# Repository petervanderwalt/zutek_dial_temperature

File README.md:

# zutek_dial_temperature
zutek_dial_temperature

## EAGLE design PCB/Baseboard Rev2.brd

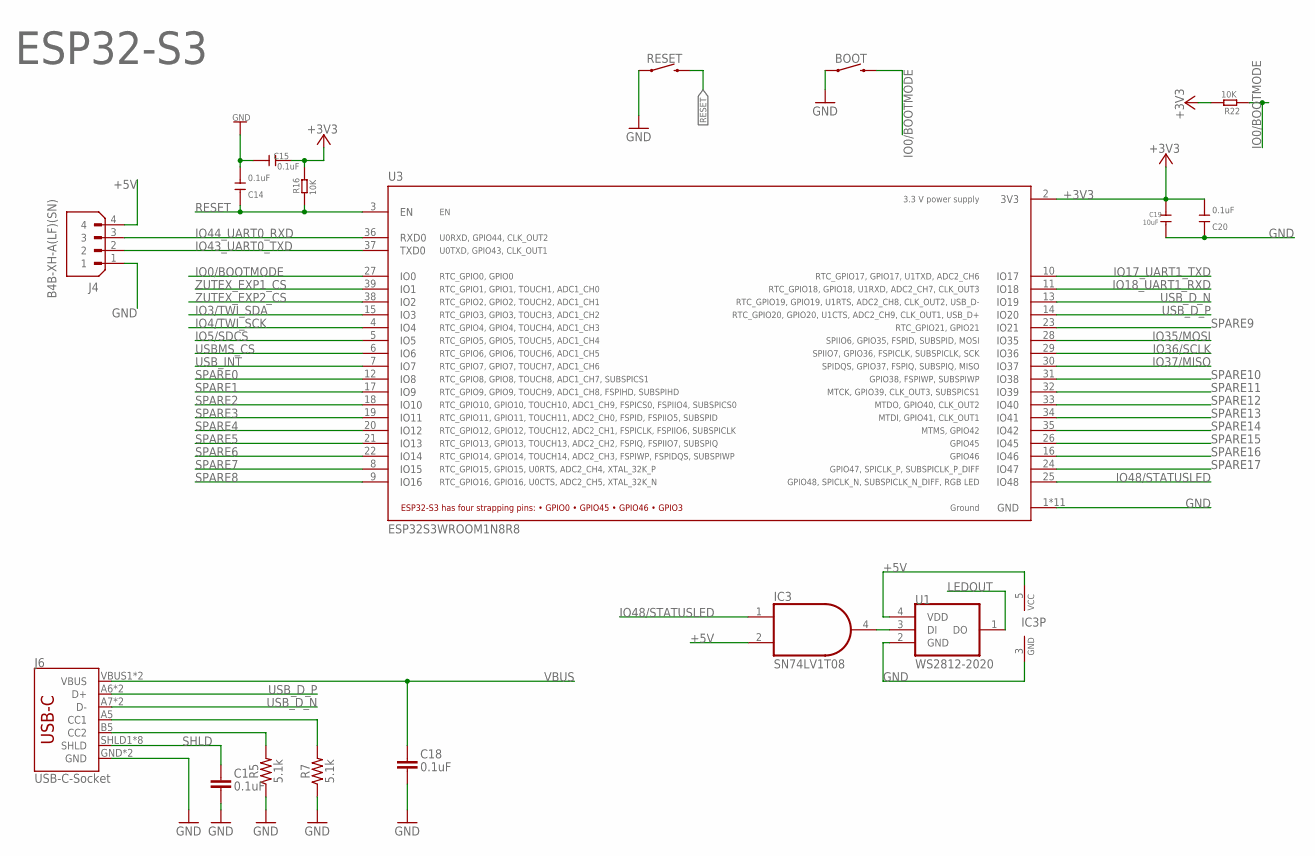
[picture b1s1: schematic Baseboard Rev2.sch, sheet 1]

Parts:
BOOT: MOMENTARY-SWITCH-SPST-SMD-6.0X3.5MM; TACTILE_SWITCH_SMD_6.0X3.5MM
C1, C18: 0.1uF; 0603-CAP
C14, C15, C20: 0.1uF; DISCRETE_C0603
C19: 10uF; C1206
IC3: SN74LV1T08; SOT23-5
J4: B4B-XH-A(LF)(SN); JST_B4B-XH-A(LF)(SN)
J6: USB-C-Socket; USB-C-16P
R5, R7: 5.1k; 0603@1
R16, R22: 10K; R0603
RESET: MOMENTARY-SWITCH-SPST-SMD-6.0X3.5MM; TACTILE_SWITCH_SMD_6.0X3.5MM
U1: WS2812-2020; LED_WS2812-2020
U3: ESP32S3WROOM1N8R8; XCVR_ESP32S3WROOM1N8R8

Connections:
+3V3: C15.1, C19.1, C20.2, R16.2, R22.2, U3.2 (3V3); also elsewhere on the board
+5V: IC3.2 (I1), IC3.5 (VCC), J4.4, U1.4 (VDD); also elsewhere on the board
CC1: J6.A5 (CC1), R7.2
CC2: J6.B5 (CC2), R5.2
GND: BOOT.1, C1.2, C14.2, C15.2, C18.2, C19.2, C20.1, IC3.3 (GND), J4.1, J6.GND, J6.GND2 (GND), R5.1, R7.1, RESET.1, U1.2 (GND), U3.1 (GND), U3.40 (GND), U3.41_1 (GND), U3.41_2 (GND), U3.41_3 (GND), U3.41_4 (GND), U3.41_5 (GND), U3.41_6 (GND), U3.41_7 (GND), U3.41_8 (GND), U3.41_9 (GND); also elsewhere on the board
IO0/BOOTMODE: BOOT.2, R22.1, U3.27 (IO0)
IO3/TWI_SDA: U3.15 (IO3); also elsewhere on the board
IO4/TWI_SCK: U3.4 (IO4); also elsewhere on the board
IO5/SDCS: U3.5 (IO5); also elsewhere on the board
IO17_UART1_TXD: U3.10 (IO17); also elsewhere on the board
IO18_UART1_RXD: U3.11 (IO18); also elsewhere on the board
IO35/MOSI: U3.28 (IO35); also elsewhere on the board
IO36/SCLK: U3.29 (IO36); also elsewhere on the board
IO37/MISO: U3.30 (IO37); also elsewhere on the board
IO43_UART0_TXD: J4.2, U3.37 (TXD0); also elsewhere on the board
IO44_UART0_RXD: J4.3, U3.36 (RXD0); also elsewhere on the board
IO48/STATUSLED: IC3.1 (I0), U3.25 (IO48)
LEDOUT: U1.1 (DO); also elsewhere on the board
unnamed: IC3.4 (O), U1.3 (DI)
RESET: C14.1, R16.1, RESET.2, U3.3 (EN); also elsewhere on the board
SHLD: C1.1, J6.SHLD1 (SHLD), J6.SHLD2 (SHLD), J6.SHLD3 (SHLD), J6.SHLD4 (SHLD), J6.SHLD5 (SHLD), J6.SHLD6 (SHLD), J6.SHLD7 (SHLD), J6.SHLD8 (SHLD)
SPARE0: U3.12 (IO8); also elsewhere on the board
SPARE1: U3.17 (IO9); also elsewhere on the board
SPARE2: U3.18 (IO10); also elsewhere on the board
SPARE3: U3.19 (IO11); also elsewhere on the board
SPARE4: U3.20 (IO12); also elsewhere on the board
SPARE5: U3.21 (IO13); also elsewhere on the board
SPARE6: U3.22 (IO14); also elsewhere on the board
SPARE7: U3.8 (IO15); also elsewhere on the board
SPARE8: U3.9 (IO16); also elsewhere on the board
SPARE9: U3.23 (IO21); also elsewhere on the board
SPARE10: U3.31 (IO38); also elsewhere on the board
SPARE11: U3.32 (IO39); also elsewhere on the board
SPARE12: U3.33 (IO40); also elsewhere on the board
SPARE13: U3.34 (IO41); also elsewhere on the board
SPARE14: U3.35 (IO42); also elsewhere on the board
SPARE15: U3.26 (IO45); also elsewhere on the board
SPARE16: U3.16 (IO46); also elsewhere on the board
SPARE17: U3.24 (IO47); also elsewhere on the board
USBMS_CS: U3.6 (IO6); also elsewhere on the board
USB_D_N: J6.A7 (D-), J6.B7 (D-), U3.13 (IO19)
USB_D_P: J6.A6 (D+), J6.B6 (D+), U3.14 (IO20)
USB_INT: U3.7 (IO7); also elsewhere on the board
VBUS: C18.1, J6.VBUS1 (VBUS), J6.VBUS2 (VBUS); also elsewhere on the board
ZUTEX_EXP1_CS: U3.39 (IO1); also elsewhere on the board
ZUTEX_EXP2_CS: U3.38 (IO2); also elsewhere on the board

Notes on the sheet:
ESP32-S3

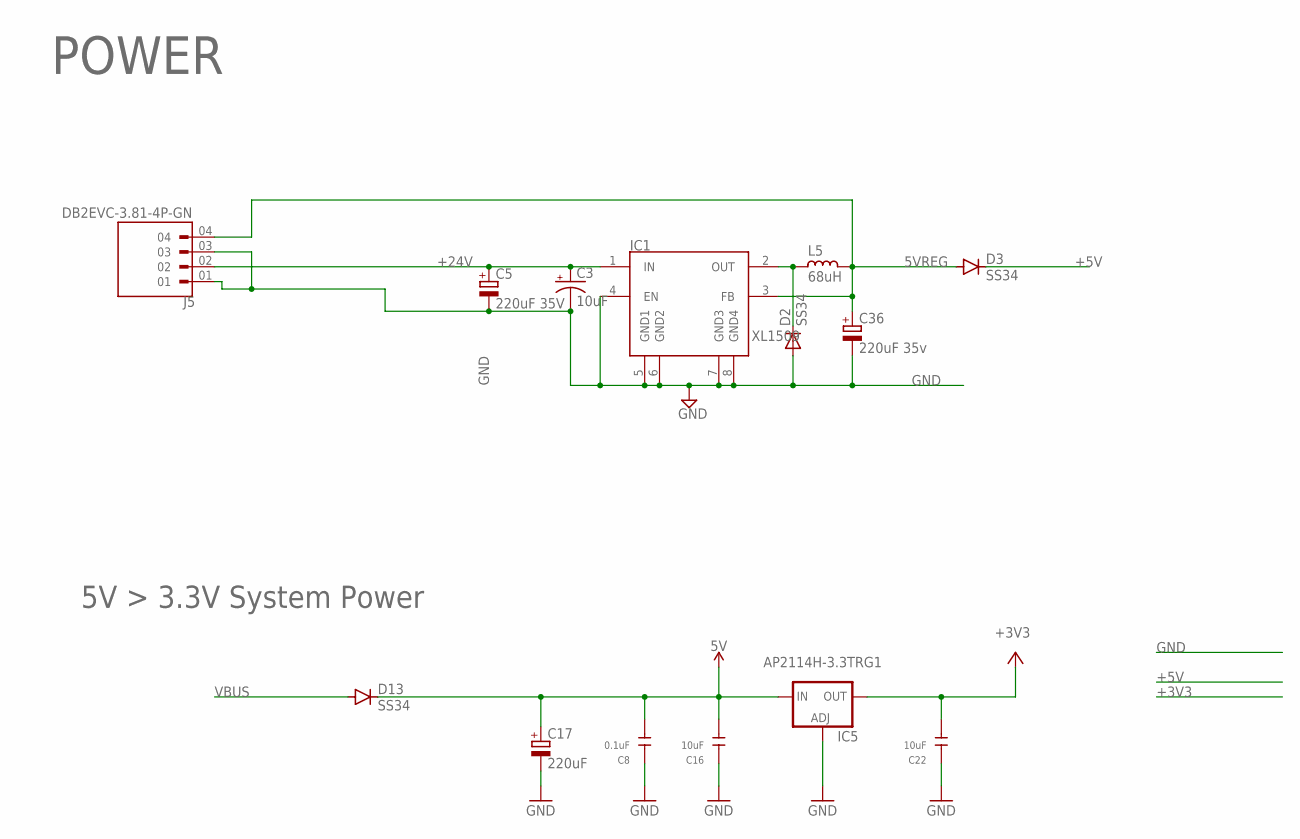
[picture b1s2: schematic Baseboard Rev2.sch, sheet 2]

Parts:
C3: 10uF; EIA3216
C5: 220uF 35V; PANASONIC_D
C8: 0.1uF; DISCRETE_C0603
C16, C22: 10uF; C1206
C17: 220uF; PANASONIC_D
C36: 220uF 35v; PANASONIC_D
D2, D3, D13: SS34; DO-214AC
IC1: XL1509; SO08
IC5: AP2114H-3.3TRG1; SOT223
J5: DB2EVC-3.81-4P-GN
L5: 68uH; CD75

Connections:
5VREG: C36.+, D3.A, IC1.3 (FB), J5.04, L5.1
+3V3: C22.1, IC5.4 (OUT); also elsewhere on the board
+5V: C8.2, C16.1, C17.+, D3.C, D13.C, IC5.3 (IN); also elsewhere on the board
+24V: C3.A (+), C5.+, IC1.1 (IN), J5.02; also elsewhere on the board
GND: C3.C (-), C5.-, C8.1, C16.2, C17.-, C22.2, C36.-, D2.2 (A), IC1.4 (EN), IC1.5 (GND1), IC1.6 (GND2), IC1.7 (GND3), IC1.8 (GND4), IC5.1 (ADJ), J5.01, J5.03; also elsewhere on the board
unnamed: D2.1 (C), IC1.2 (OUT), L5.2
VBUS: D13.A; also elsewhere on the board

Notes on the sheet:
5V > 3.3V System Power
POWER

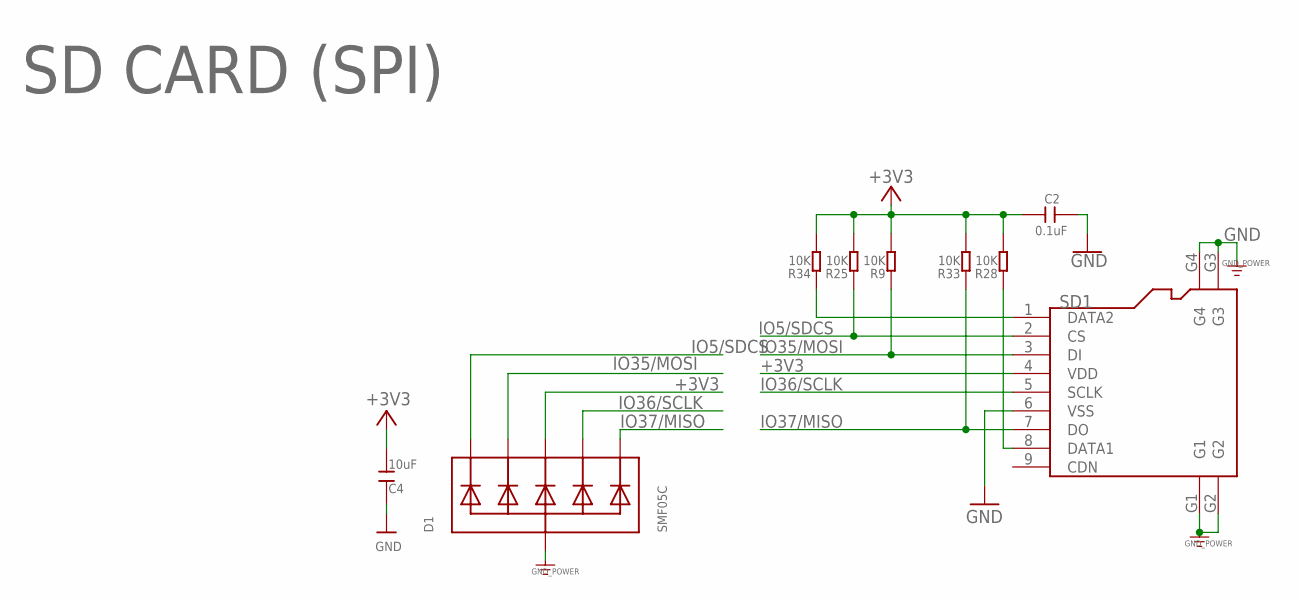
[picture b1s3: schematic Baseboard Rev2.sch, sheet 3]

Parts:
C2: 0.1uF; DISCRETE_C0603
C4: 10uF; DISCRETE_C1206
D1: SMF05C; SOT363
R9, R25, R28, R33, R34: 10K; DISCRETE_R0603
SD1: HOLDER-MICROSD-9P; 9P-SMD-W/-RING

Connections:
+3V3: C2.2, C4.2, D1.4 (C3), R9.2, R25.2, R28.2, R33.2, R34.2, SD1.4 (VDD); also elsewhere on the board
GND: C2.1, C4.1, D1.2 (A), SD1.6 (VSS), SD1.G1, SD1.G2, SD1.G3, SD1.G4; also elsewhere on the board
IO5/SDCS: D1.1 (C1), R25.1, SD1.2 (CS); also elsewhere on the board
IO35/MOSI: D1.3 (C2), R9.1, SD1.3 (DI); also elsewhere on the board
IO36/SCLK: D1.5 (C4), SD1.5 (SCLK); also elsewhere on the board
IO37/MISO: D1.6 (C5), R33.1, SD1.7 (DO); also elsewhere on the board
unnamed: R34.1, SD1.1 (DATA2)
unnamed: R28.1, SD1.8 (DATA1)

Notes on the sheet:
SD CARD (SPI)

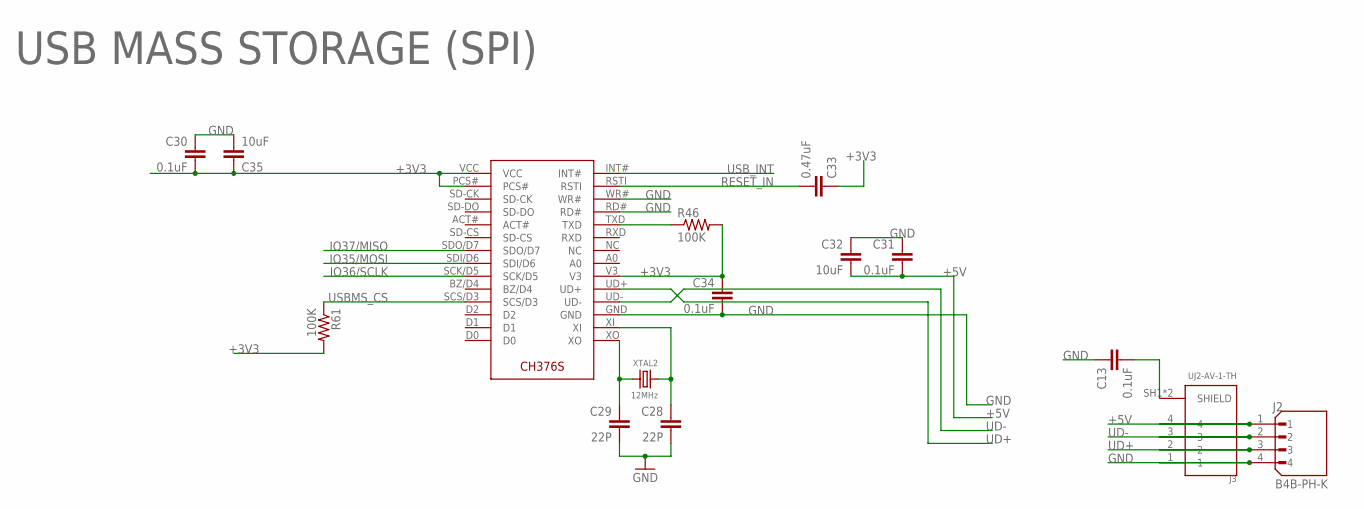
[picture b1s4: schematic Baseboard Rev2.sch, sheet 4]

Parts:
C13, C30, C31, C34: 0.1uF; C0603
C28, C29: 22P; C0603
C32, C35: 10uF; C1206
C33: 0.47uF; C0603
IC2: CH376; CH376S-SOIC
J2: B4B-PH-K; JST_B4B-PH-K
J3: UJ2-AV-1-TH; CUI_UJ2-AV-1-TH
R46, R61: 100K; R0603
XTAL2: 12MHz; CRYSTAL_3.2X2.5

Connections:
+3V3: C30.2, C33.1, C34.1, C35.1, IC2.PCS#, IC2.V3, IC2.VCC, R46.2, R61.2; also elsewhere on the board
+5V: C31.2, C32.2, J2.1, J3.4; also elsewhere on the board
GND: C13.1, C28.2, C29.2, C30.1, C31.1, C32.1, C34.2, C35.2, IC2.GND, IC2.RD#, IC2.WR#, J2.4, J3.1; also elsewhere on the board
IO35/MOSI: IC2.SDI/D6; also elsewhere on the board
IO36/SCLK: IC2.SCK/D5; also elsewhere on the board
IO37/MISO: IC2.SDO/D7; also elsewhere on the board
unnamed: C13.2, J3.SH1 (SHIELD), J3.SH2 (SHIELD)
unnamed: C28.1, IC2.XI, XTAL2.1
unnamed: C29.1, IC2.XO, XTAL2.2
unnamed: IC2.TXD, R46.1
RESET_IN: C33.2, IC2.RSTI
UD+: IC2.UD+, J2.3, J3.2
UD-: IC2.UD-, J2.2, J3.3
USBMS_CS: IC2.SCS/D3, R61.1; also elsewhere on the board
USB_INT: IC2.INT#; also elsewhere on the board

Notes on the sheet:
USB MASS STORAGE (SPI)

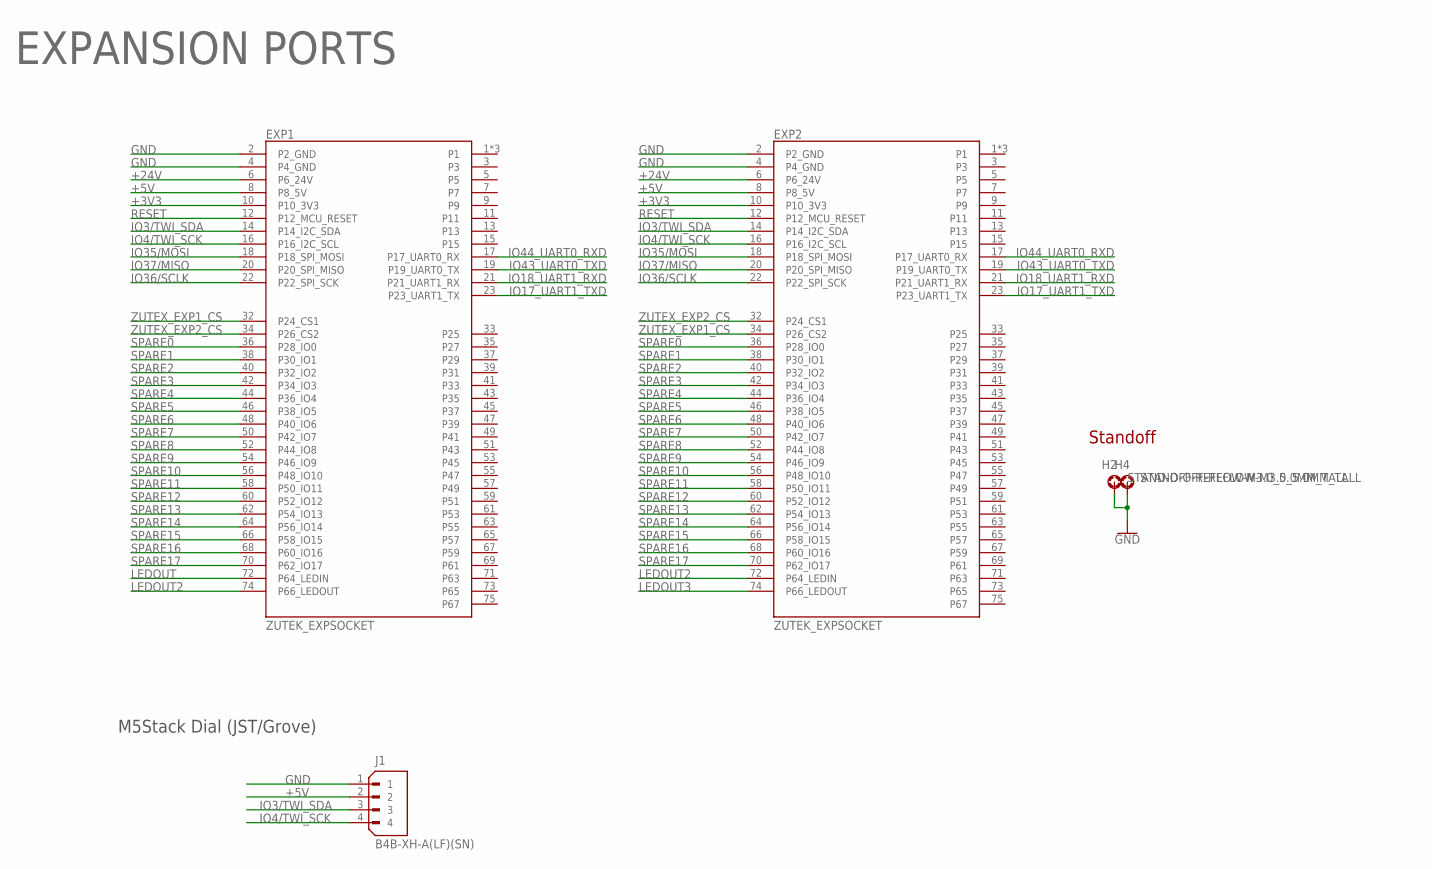
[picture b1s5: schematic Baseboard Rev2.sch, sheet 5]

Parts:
EXP1, EXP2: ZUTEK_EXPSOCKET; M.2-CONNECTOR-E-ZUTEK
H2, H4: STAND-OFF-REFLOW-M3.0_5.0MM_TALL; STAND-OFF-REFLOW-M3.0
J1: B4B-XH-A(LF)(SN); JST_B4B-XH-A(LF)(SN)

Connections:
+3V3: EXP1.10 (P10_3V3), EXP2.10 (P10_3V3); also elsewhere on the board
+5V: EXP1.8 (P8_5V), EXP2.8 (P8_5V), J1.2; also elsewhere on the board
+24V: EXP1.6 (P6_24V), EXP2.6 (P6_24V); also elsewhere on the board
GND: EXP1.2 (P2_GND), EXP1.4 (P4_GND), EXP2.2 (P2_GND), EXP2.4 (P4_GND), H2.1, H4.1, J1.1; also elsewhere on the board
IO3/TWI_SDA: EXP1.14 (P14_I2C_SDA), EXP2.14 (P14_I2C_SDA), J1.3; also elsewhere on the board
IO4/TWI_SCK: EXP1.16 (P16_I2C_SCL), EXP2.16 (P16_I2C_SCL), J1.4; also elsewhere on the board
IO17_UART1_TXD: EXP1.23 (P23_UART1_TX), EXP2.23 (P23_UART1_TX); also elsewhere on the board
IO18_UART1_RXD: EXP1.21 (P21_UART1_RX), EXP2.21 (P21_UART1_RX); also elsewhere on the board
IO35/MOSI: EXP1.18 (P18_SPI_MOSI), EXP2.18 (P18_SPI_MOSI); also elsewhere on the board
IO36/SCLK: EXP1.22 (P22_SPI_SCK), EXP2.22 (P22_SPI_SCK); also elsewhere on the board
IO37/MISO: EXP1.20 (P20_SPI_MISO), EXP2.20 (P20_SPI_MISO); also elsewhere on the board
IO43_UART0_TXD: EXP1.19 (P19_UART0_TX), EXP2.19 (P19_UART0_TX); also elsewhere on the board
IO44_UART0_RXD: EXP1.17 (P17_UART0_RX), EXP2.17 (P17_UART0_RX); also elsewhere on the board
LEDOUT: EXP1.72 (P64_LEDIN); also elsewhere on the board
LEDOUT2: EXP1.74 (P66_LEDOUT), EXP2.72 (P64_LEDIN)
LEDOUT3: EXP2.74 (P66_LEDOUT)
RESET: EXP1.12 (P12_MCU_RESET), EXP2.12 (P12_MCU_RESET); also elsewhere on the board
SPARE0: EXP1.36 (P28_IO0), EXP2.36 (P28_IO0); also elsewhere on the board
SPARE1: EXP1.38 (P30_IO1), EXP2.38 (P30_IO1); also elsewhere on the board
SPARE2: EXP1.40 (P32_IO2), EXP2.40 (P32_IO2); also elsewhere on the board
SPARE3: EXP1.42 (P34_IO3), EXP2.42 (P34_IO3); also elsewhere on the board
SPARE4: EXP1.44 (P36_IO4), EXP2.44 (P36_IO4); also elsewhere on the board
SPARE5: EXP1.46 (P38_IO5), EXP2.46 (P38_IO5); also elsewhere on the board
SPARE6: EXP1.48 (P40_IO6), EXP2.48 (P40_IO6); also elsewhere on the board
SPARE7: EXP1.50 (P42_IO7), EXP2.50 (P42_IO7); also elsewhere on the board
SPARE8: EXP1.52 (P44_IO8), EXP2.52 (P44_IO8); also elsewhere on the board
SPARE9: EXP1.54 (P46_IO9), EXP2.54 (P46_IO9); also elsewhere on the board
SPARE10: EXP1.56 (P48_IO10), EXP2.56 (P48_IO10); also elsewhere on the board
SPARE11: EXP1.58 (P50_IO11), EXP2.58 (P50_IO11); also elsewhere on the board
SPARE12: EXP1.60 (P52_IO12), EXP2.60 (P52_IO12); also elsewhere on the board
SPARE13: EXP1.62 (P54_IO13), EXP2.62 (P54_IO13); also elsewhere on the board
SPARE14: EXP1.64 (P56_IO14), EXP2.64 (P56_IO14); also elsewhere on the board
SPARE15: EXP1.66 (P58_IO15), EXP2.66 (P58_IO15); also elsewhere on the board
SPARE16: EXP1.68 (P60_IO16), EXP2.68 (P60_IO16); also elsewhere on the board
SPARE17: EXP1.70 (P62_IO17), EXP2.70 (P62_IO17); also elsewhere on the board
ZUTEX_EXP1_CS: EXP1.32 (P24_CS1), EXP2.34 (P26_CS2); also elsewhere on the board
ZUTEX_EXP2_CS: EXP1.34 (P26_CS2), EXP2.32 (P24_CS1); also elsewhere on the board

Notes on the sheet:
M5Stack Dial (JST/Grove)
EXPANSION PORTS
Standoff

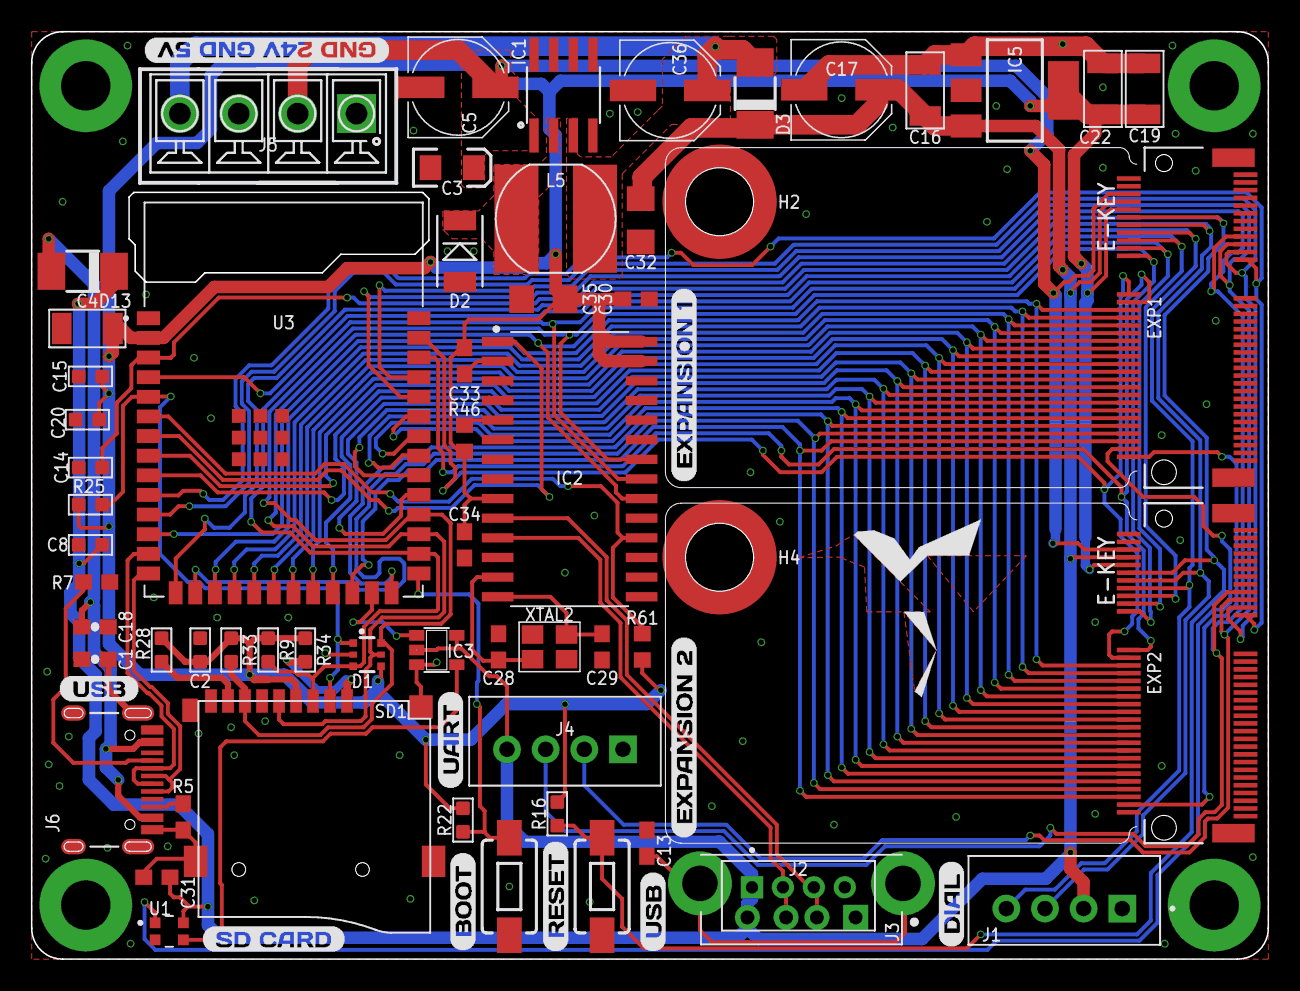
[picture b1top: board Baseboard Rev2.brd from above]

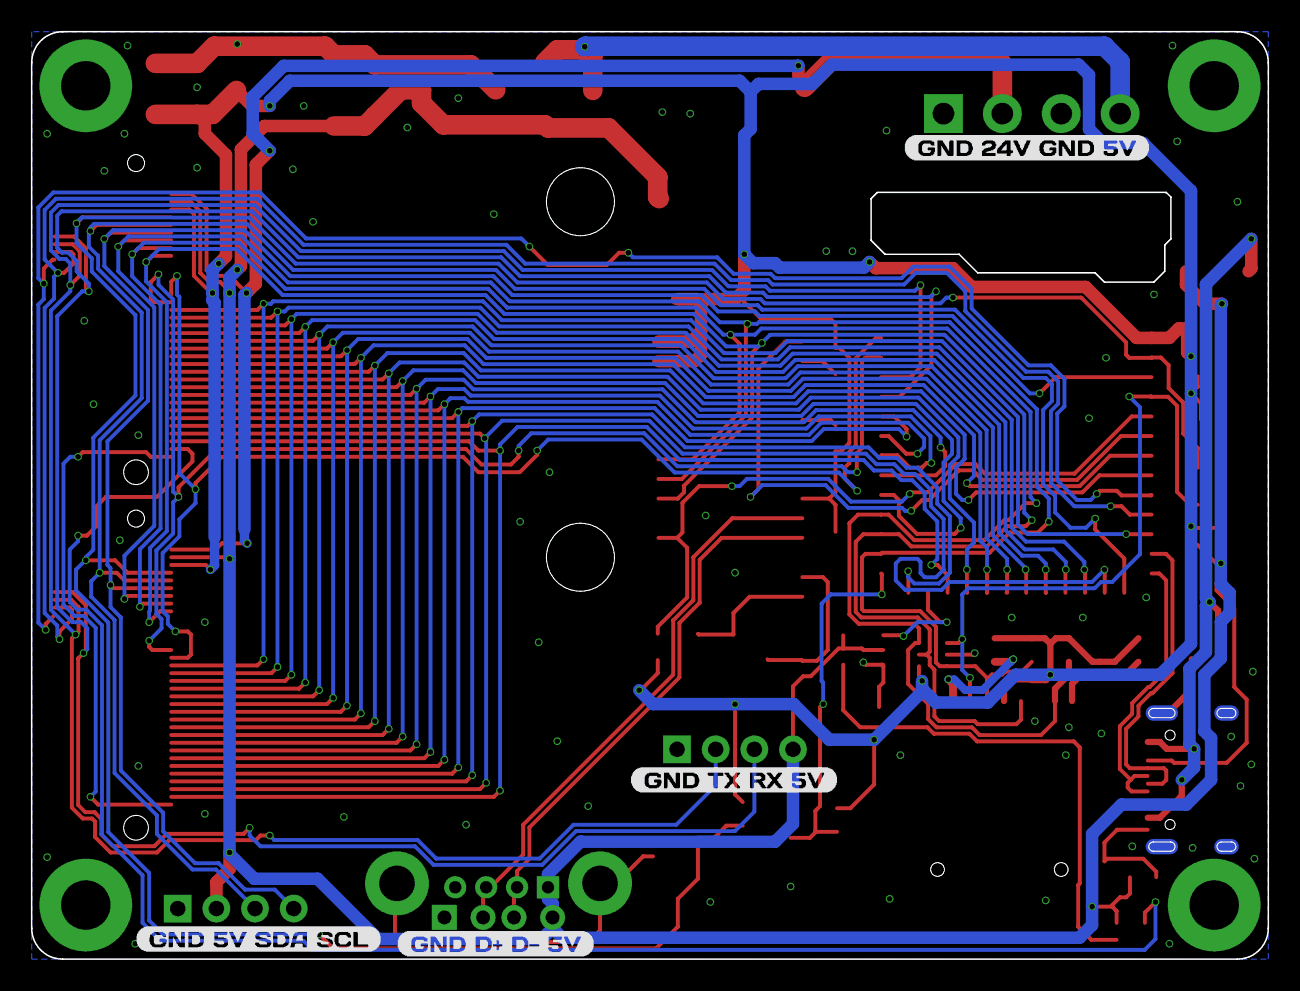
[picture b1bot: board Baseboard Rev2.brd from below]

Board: 2 copper layers, 80.0 x 60.0 mm, 74 parts (4 on the bottom side), 59 nets.

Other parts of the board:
U$1: DIAL0
U$2: EXPANSION_10
U$4: GND_5V_SDA_SCL0
U$6: EXPANSION_20
U$7: GND_D#_D#_5V0
U$8: GND_TX_RX_5V0
U$9, U$28: GND_24V_GND_5V0
U$16, U$25: USB0
U$23: BOOT0
U$24: RESET0
U$26: SD_CARD0
U$27: UART0

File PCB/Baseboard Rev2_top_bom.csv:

Comment,Designator,Footprint,LCSC Part #
0.1uF, C1 C2 C8 C13 C14 C15 C18 C20 C30 C31 C34,C0603,C14663
0.47uF,C33,C0603,C513577
5.1k,R5 R7,R0603,C2907044
10K,R9 R16 R22 R25 R28 R33 R34,R0603,C98220
10uF,C3 C4 C16 C19 C22 C32 C35,C1206,C454102
12MHz,XTAL2,CRYSTAL_3.2X2.5,C5280582
22P,C28 C29,C0603,C105620
68uH,L5,CD75,C5289451 
100K,R46 R61,R0603,C14675
220uF,C5 C17 C36,6.3mm SMD,C7471881
AP2114H-3.3TRG1,IC5,SOT223,C150716
CH376S,IC2,CH376S-SOIC,C14166
ESP32S3WROOM1N8R8,U3,XCVR_ESP32S3WROOM1N8R8,C2913204
MOMENTARY-SWITCH-SPST-SMD-6.0X3.5MM,BOOT RESET,TACTILE_SWITCH_SMD_6.0X3.5MM,C118141 
SMF05C,D1,SOT363,C15879
SN74LV1T08,IC3,SOT23-5,C130199
SS34,D2 D3 D13,DO-214AC,C8678
USB-C-Socket,J6,USB-C-16P,C2765186
WS2812-2020,U1,LED_WS2812-2020,C965555
XL1509-5.0,IC1,SO08,C61063
m.2 e key socket,EXP1 EXP2,M.2-CONNECTOR-E-3MM HEIGHT,C3020019
REFLOW NUT M2.5,H2 H4,SMTSOM330BTR M3 THREAD 3MM HEIGHT,C5221843
SD CARD SOCKET,SD1,CONN MICRO SD CARD (TF CARD) SMD,C91145
DB2EVC-3.81-4P-GN,J5,"Green Straight Pin Plugin,P=3.81mm Pluggable System Terminal Block ROHS ",C8410 
B4B-XH-A(LF)(SN),J4 J1,XH-4A ,C2908602
USB-A VERTICAL,J3,USB-A VERTICAL,C456015

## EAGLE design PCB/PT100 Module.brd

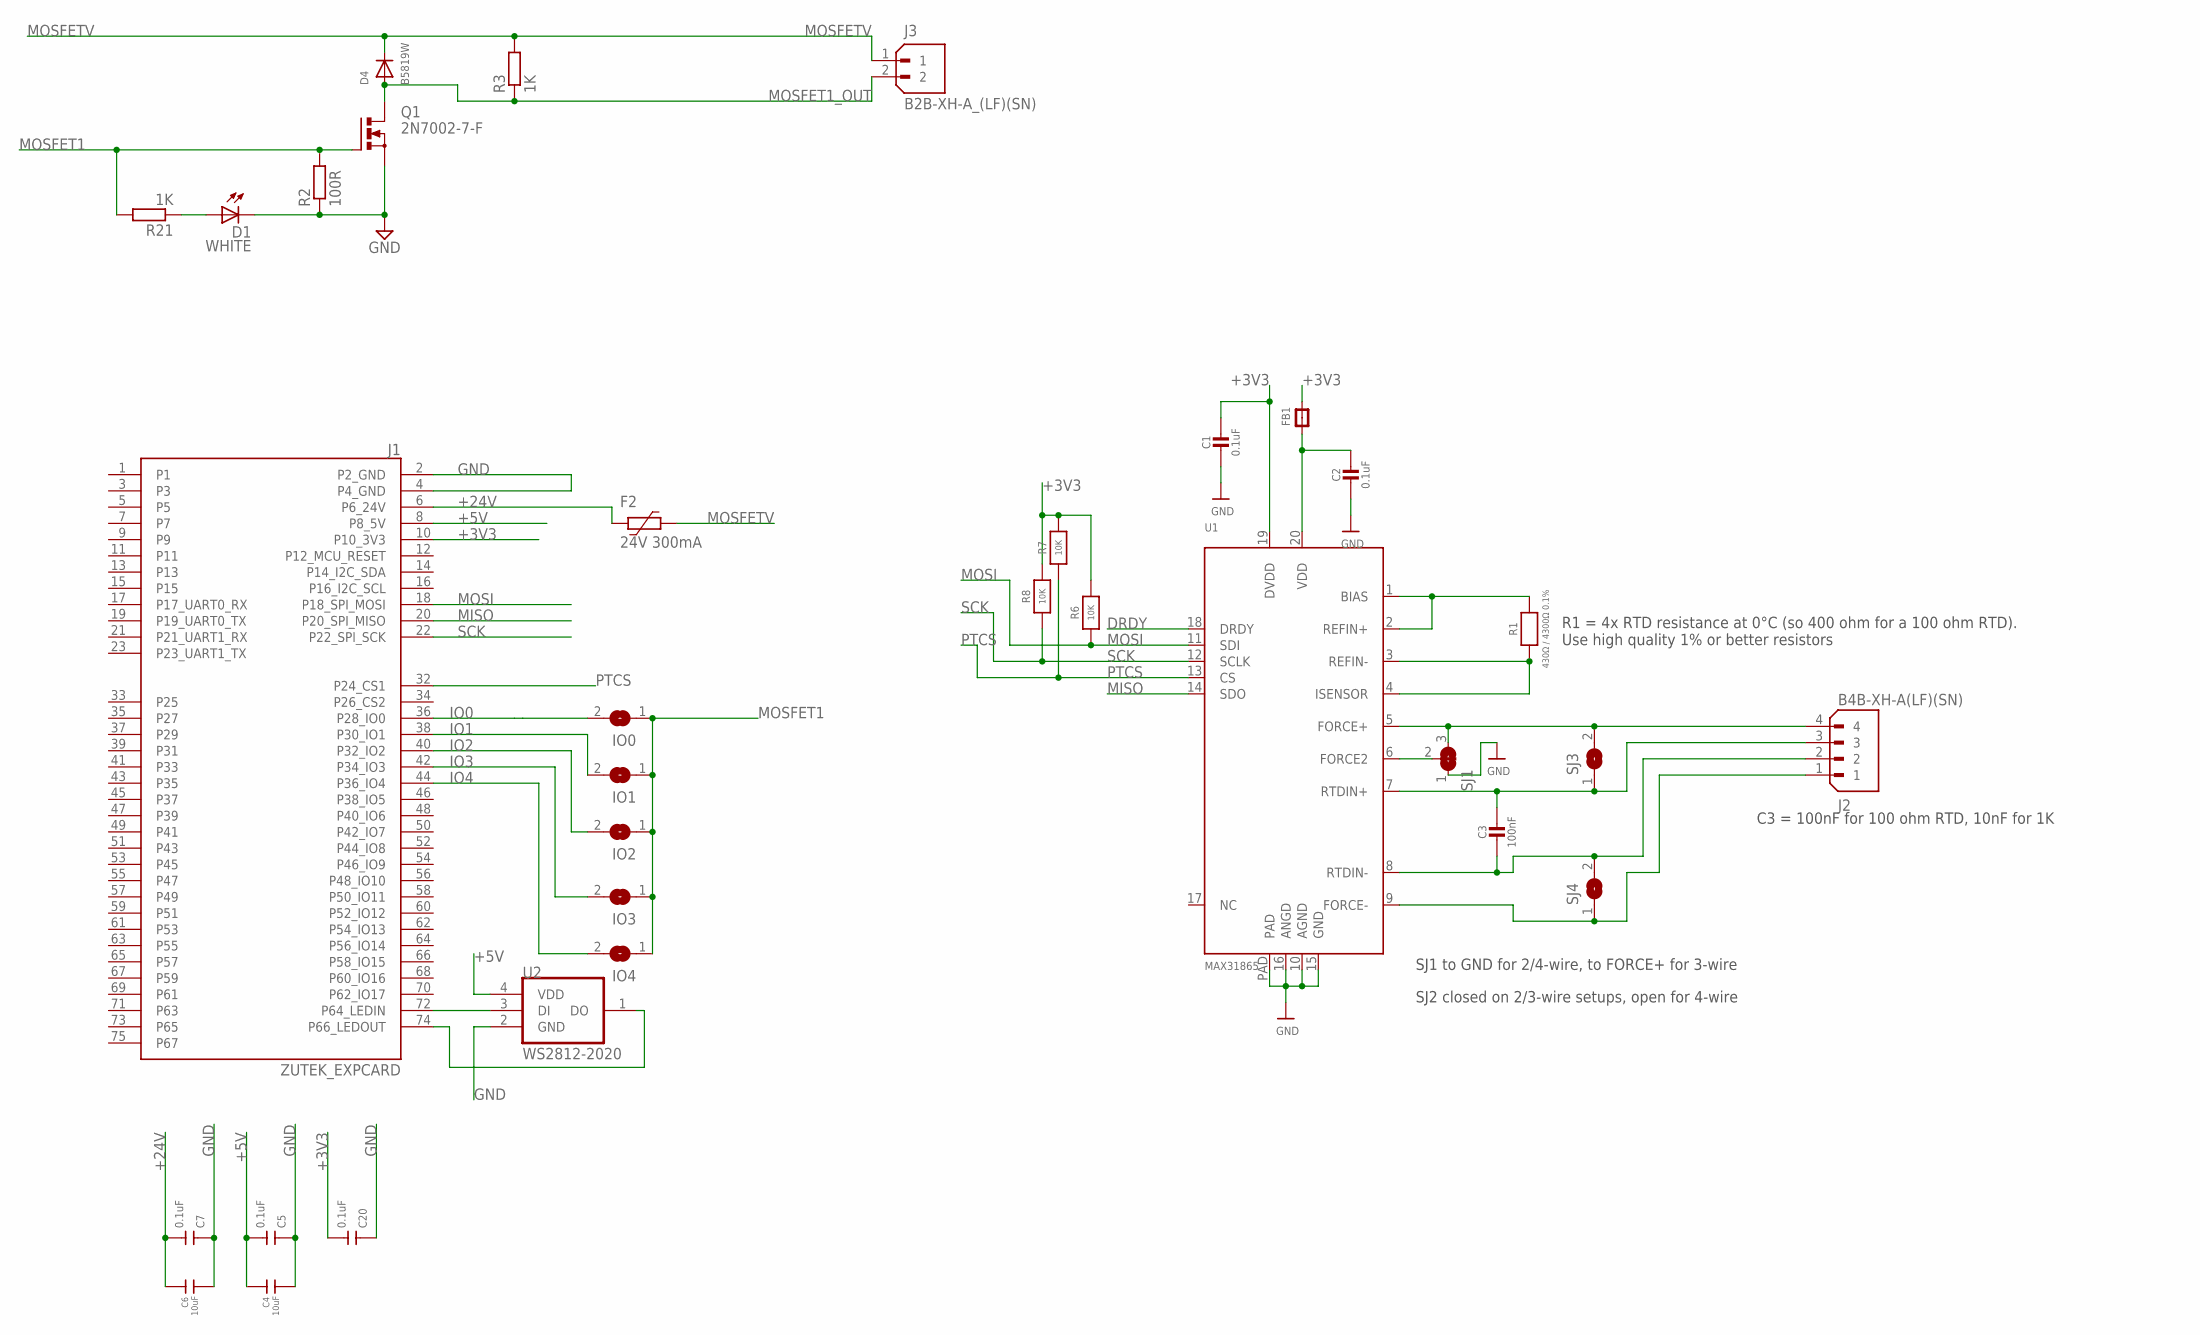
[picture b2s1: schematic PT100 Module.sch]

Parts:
C1, C2: 0.1uF; 0805-NO
C3: 100nF; 0805-NO
C4, C6: 10uF; C1206
C5, C7, C20: 0.1uF; DISCRETE_C0603
D1: WHITE; CHIP-LED0603
D4: B5819W; SOD123FL
F2: 24V 300mA; 1206L
FB1: FERRITE-0805NO; 0805-NO
IO0: SOLDERJUMPERCLOSED; SOLDERJUMPER_CLOSEDWIRE
IO1, IO2, IO3, IO4: SOLDERJUMPER; SOLDERJUMPER_ARROW_NOPASTE
J1: ZUTEK_EXPCARD; M.2-CARD-E-22-ZUTEK
J2: B4B-XH-A(LF)(SN); JST_B4B-XH-A(LF)(SN)
J3: B2B-XH-A_(LF)(SN); JST_B2B-XH-A_(LF)(SN)
Q1: 2N7002-7-F; SOT-23
R1: 430Ω / 4300Ω 0.1%; 0805-NO
R2: 100R; R0402
R3: 1K; R0402; LCSC_PART C11702
R6, R7, R8: 10K; _0402
R21: 1K; R0402
SJ1: SOLDERJUMPER_2WAY; SOLDERJUMPER_2WAY_OPEN_NOPASTE
SJ3, SJ4: SOLDERJUMPER; SOLDERJUMPER_ARROW_NOPASTE
U1: MAX31865; QFN20_4MM_0.65MM
U2: WS2812-2020; LED_WS2812-2020

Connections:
+3V3: C1.1, C20.2, FB1.2, J1.10 (P10_3V3), R6.2, R7.2, R8.2, U1.19 (DVDD)
+5V: C4.1, C5.2, J1.8 (P8_5V), U2.4 (VDD)
+24V: C6.1, C7.2, F2.2, J1.6 (P6_24V)
DRDY: U1.18 (DRDY)
FORCE+: J2.4, SJ1.3, SJ3.2, U1.5 (FORCE+)
FORCE-: J2.1, SJ4.1, U1.9 (FORCE-)
GND: C1.2, C2.2, C4.2, C5.1, C6.2, C7.1, C20.1, D1.C, J1.2 (P2_GND), J1.4 (P4_GND), Q1.P2 (S), R2.1, SJ1.1, U1.10 (AGND), U1.15 (GND), U1.16 (ANGD), U1.PAD, U2.2 (GND)
IO0: IO0.2, J1.36 (P28_IO0)
IO1: IO1.2, J1.38 (P30_IO1)
IO2: IO2.2, J1.40 (P32_IO2)
IO3: IO3.2, J1.42 (P34_IO3)
IO4: IO4.2, J1.44 (P36_IO4)
MISO: J1.20 (P20_SPI_MISO), U1.14 (SDO)
MOSFET1: IO0.1, IO1.1, IO2.1, IO3.1, IO4.1, Q1.P1 (G), R2.2, R21.2
MOSFET1_OUT: D4.A, J3.2, Q1.P3 (D), R3.1
MOSFETV: D4.C, F2.1, J3.1, R3.2
MOSI: J1.18 (P18_SPI_MOSI), R6.1, U1.11 (SDI)
unnamed: R1.1, U1.3 (REFIN-), U1.4 (ISENSOR)
unnamed: R1.2, U1.1 (BIAS), U1.2 (REFIN+)
unnamed: C2.1, FB1.1, U1.20 (VDD)
unnamed: D1.A, R21.1
unnamed: J1.72 (P64_LEDIN), U2.3 (DI)
unnamed: SJ1.2, U1.6 (FORCE2)
unnamed: J1.74 (P66_LEDOUT), U2.1 (DO)
PTCS: J1.32 (P24_CS1), R7.1, U1.13 (CS)
RTDIN+: C3.1, J2.3, SJ3.1, U1.7 (RTDIN+)
RTDIN-: C3.2, J2.2, SJ4.2, U1.8 (RTDIN-)
SCK: J1.22 (P22_SPI_SCK), R8.1, U1.12 (SCLK)

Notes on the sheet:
C3 = 100nF for 100 ohm RTD, 10nF for 1K
R1 = 4x RTD resistance at 0°C (so 400 ohm for a 100 ohm RTD). Use high quality 1% or better resistors
SJ1 to GND for 2/4-wire, to FORCE+ for 3-wire
SJ2 closed on 2/3-wire setups, open for 4-wire

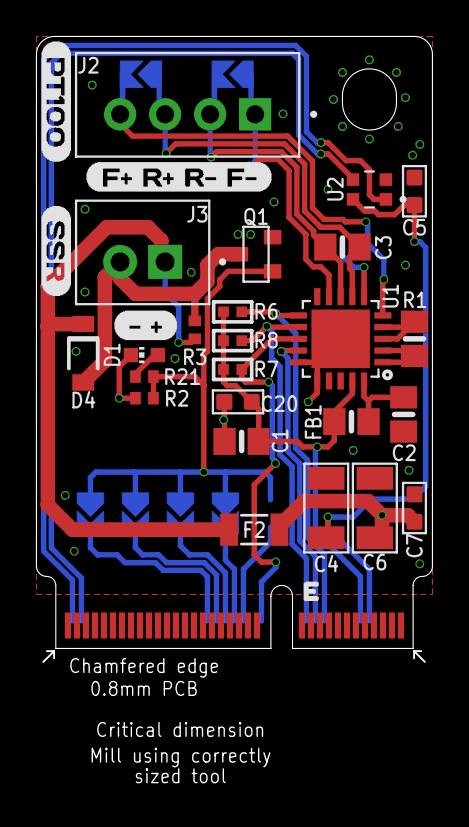
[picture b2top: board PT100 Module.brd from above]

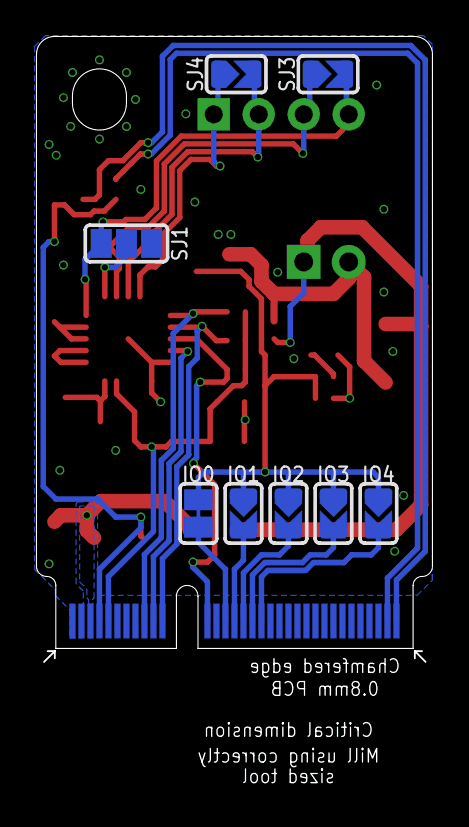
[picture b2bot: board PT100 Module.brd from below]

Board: 2 copper layers, 21.9 x 41.8 mm, 37 parts (8 on the bottom side), 27 nets.

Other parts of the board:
U$4: PT1000
U$5: SSR0
U$7: #_#0
U$8: F#_R#_R#_F#0

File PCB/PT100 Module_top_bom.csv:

Comment,Designator,Footprint,LCSC Part #
Ferrite Bead,FB1,F0805,C85840
0.1uF, C1 C2,C0805,C49678
0.1uF,C5 C7 C20,DISCRETE_C0603,C14663
1K,R3 R21,R0402,C106235
ST3422A,Q1,SOT-23,C2682907
10K,R6 R7 R8,_0402,C60490
10uF,C4 C6,C1206,C13585
24V 300mA,F2,1206L,C70073
100R,R2,R0402,C60490
100nF,C3,0805-NO,C49678
430Ω / 4300Ω 0.1%,R1,0805-NO,C318148
B5819W,D4,SOD123FL,C64885
MAX31865,U1,QFN20_4MM_0.65MM,C118474
WHITE,D1,CHIP-LED0603,C83904
WS2812-2020,U2,LED_WS2812-2020,C965555
B4B-XH-A(LF)(SN),J2,JST XH 4P,C2908602
B2B-XH-A_(LF)(SN),J3,JST XH 2P,C158012

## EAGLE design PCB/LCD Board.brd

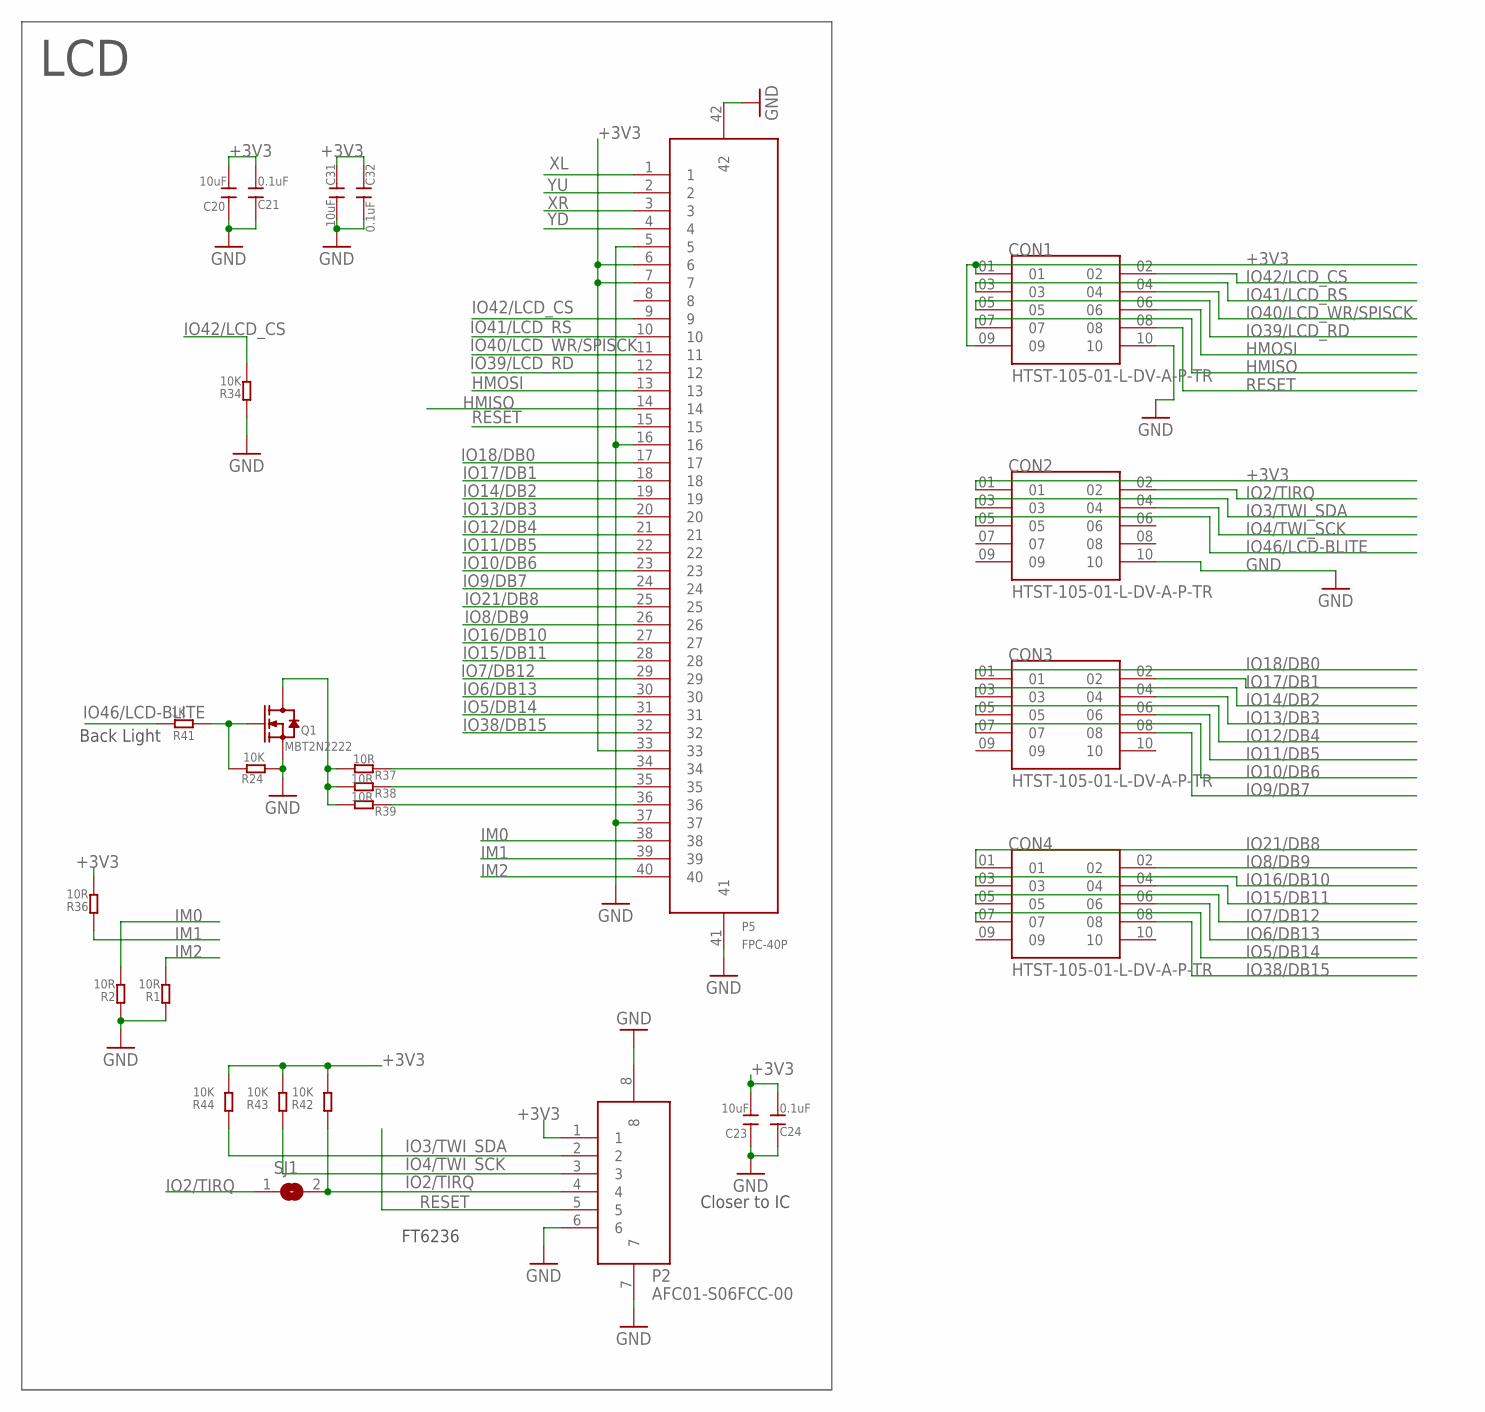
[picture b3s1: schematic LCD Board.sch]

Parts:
C20, C23, C31: 10uF; DISCRETE_C1206
C21, C24, C32: 0.1uF; DISCRETE_C0603
CON1, CON2, CON3, CON4: HTST-105-01-L-DV-A-P-TR; SAMTEC_HTST-105-01-L-DV-A-P-TR
P2: AFC01-S06FCC-00; SMD8-50P-740L535W
P5: FPC-40P; SMD42-50P-2560L490W
Q1: MBT2N2222; SOT23@1
R1, R2, R36, R37, R38, R39: 10R; DISCRETE_R0603
R24, R34, R42, R43, R44: 10K; DISCRETE_R0603
R41: 1K; DISCRETE_R0603
SJ1: SJ

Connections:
+3V3: C20.2, C21.2, C23.2, C24.2, C31.1, C32.1, CON1.01, CON1.09, CON2.01, P2.1, P5.6, P5.7, P5.33, R36.2, R42.2, R43.2, R44.2
GND: C20.1, C21.1, C23.1, C24.1, C31.2, C32.2, CON1.10, CON2.10, P2.6, P2.7, P2.8, P5.5, P5.16, P5.37, P5.41, P5.42, Q1.2 (S), R1.1, R2.1, R24.1, R34.1
HMISO: CON1.07, P5.14
HMOSI: CON1.06, P5.13
IM0: P5.38, R2.2
IM1: P5.39, R36.1
IM2: P5.40, R1.2
IO2/TIRQ: CON2.02, P2.4, R42.1, SJ1.1, SJ1.2
IO3/TWI_SDA: CON2.03, P2.2, R44.1
IO4/TWI_SCK: CON2.04, P2.3, R43.1
IO5/DB14: CON4.07, P5.31
IO6/DB13: CON4.06, P5.30
IO7/DB12: CON4.05, P5.29
IO8/DB9: CON4.02, P5.26
IO9/DB7: CON3.08, P5.24
IO10/DB6: CON3.07, P5.23
IO11/DB5: CON3.06, P5.22
IO12/DB4: CON3.05, P5.21
IO13/DB3: CON3.04, P5.20
IO14/DB2: CON3.03, P5.19
IO15/DB11: CON4.04, P5.28
IO16/DB10: CON4.03, P5.27
IO17/DB1: CON3.02, P5.18
IO18/DB0: CON3.01, P5.17
IO21/DB8: CON4.01, P5.25
IO38/DB15: CON4.08, P5.32
IO39/LCD_RD: CON1.05, P5.12
IO40/LCD_WR/SPISCK: CON1.04, P5.11
IO41/LCD_RS: CON1.03, P5.10
IO42/LCD_CS: CON1.02, P5.9, R34.2
IO46/LCD-BLITE: CON2.05, R41.2
unnamed: P5.34, R37.1
unnamed: P5.35, R38.1
unnamed: P5.36, R39.1
unnamed: Q1.1 (G), R24.2, R41.1
unnamed: Q1.3 (D), R37.2, R38.2, R39.2
RESET: CON1.08, P2.5, P5.15
XL: P5.1
XR: P5.3
YD: P5.4
YU: P5.2

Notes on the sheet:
FT6236
Closer to IC
Back Light
LCD

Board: 2 copper layers, 26 parts (0 on the bottom side), 37 nets, no tracks yet.

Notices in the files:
parts and their libraries:
microbuilder: This work is placed in the public domain, and may be freely used for commercial and non-commercial work with the following conditions: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
SparkFun-Connectors: Licensing: Creative Commons ShareAlike 4.0 International - https://creativecommons.org/licenses/by-sa/4.0
